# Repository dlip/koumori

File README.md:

# Koumori Keyboard

- Designed to be minimalistic and portable
- 28 keys (Using Engram with my [layout](https://github.com/dlip/qmk_firmware/blob/dlip/keyboards/dlip/koumori/keymaps/engram/README.md))
- Unibody design
- RP2040-Zero MCU
- Cirque 40mm trackpad with glass overlay
- Customizable layout with QMK Firmware
- Case with handle and magnetic lid
- PCB and case designed in [Ergogen](https://ergogen.xyz)
- Simple [build guide](./build.md) with no microscopic parts
- Name means the animal "bat" in Japanese
- Open source and free (GPL-3.0)

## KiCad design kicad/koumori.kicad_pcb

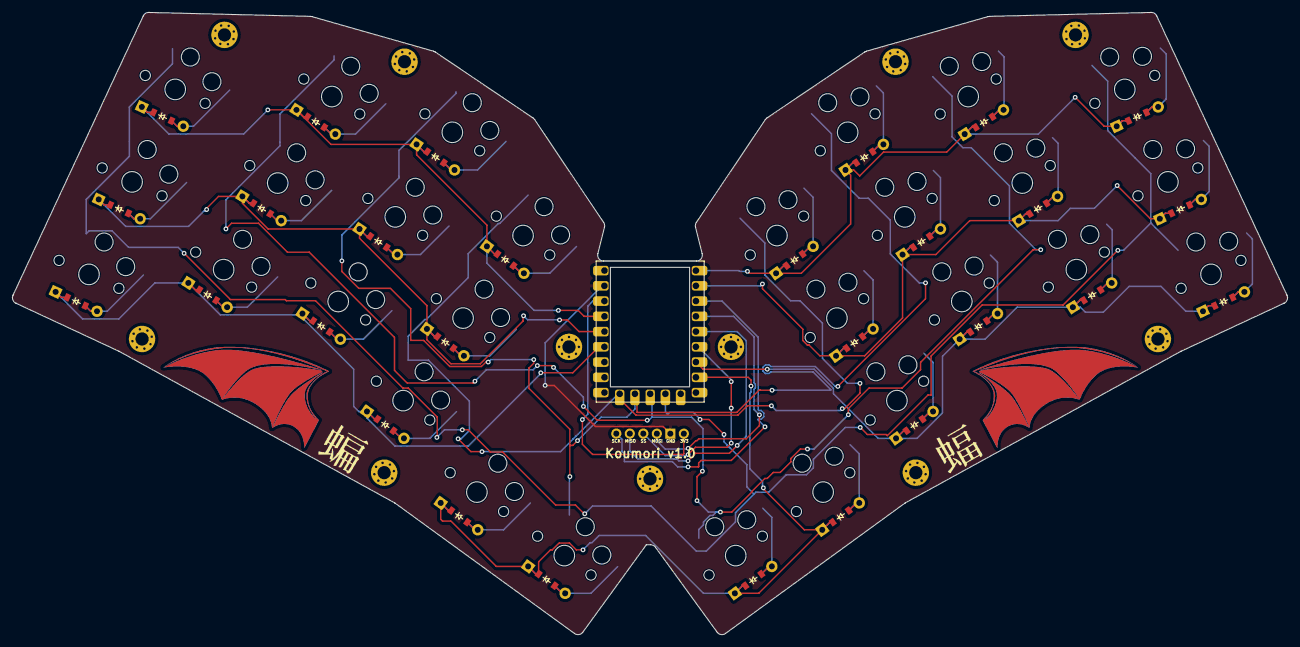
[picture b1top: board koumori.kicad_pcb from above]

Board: 2 copper layers, 212.4 x 103.7 mm, 69 parts (0 on the bottom side), 45 nets.

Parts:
D1, D2, D3, D4, D5, D6, D7, D8, D9, D10, D11, D12, D13, D14, D15, D16, D17, D18, D19, D20, D21, D22, D23, D24, D25, D26, D27, D28: ComboDiode
Pointing1: Pointing-connector
RP2040Zero1: RP2040-Zero
S1, S2, S3, S4, S5, S6, S7, S8, S9, S10, S11, S12, S13, S14, S15, S16, S17, S18, S19, S20, S21, S22, S23, S24, S25, S26, S27, S28: PG1350
_1, _2, _3, _4, _5, _6, _7, _8, _9, _10, _11: MountingHole_2.2mm_M2_Pad_Via

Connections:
GND: Pointing1.5, RP2040Zero1.20
GP0: D17.1, D20.1, D23.1, D26.1, RP2040Zero1.1
GP1: D16.1, D19.1, D22.1, D25.1, RP2040Zero1.2
GP2: Pointing1.1, RP2040Zero1.3
GP3: Pointing1.4, RP2040Zero1.4
GP4: Pointing1.2, RP2040Zero1.5
GP5: Pointing1.3, RP2040Zero1.6
GP6: D15.1, D18.1, D21.1, D24.1, RP2040Zero1.7
GP7: D13.1, D14.1, D27.1, D28.1, RP2040Zero1.8
GP10: RP2040Zero1.11, S1.1, S2.1, S3.1, S15.1, S16.1, S17.1, S27.1
GP11: RP2040Zero1.12, S4.1, S5.1, S6.1, S18.1, S19.1, S20.1, S28.1
GP12: RP2040Zero1.13, S7.1, S8.1, S9.1, S14.1, S21.1, S22.1, S23.1
GP13: RP2040Zero1.14, S10.1, S11.1, S12.1, S13.1, S24.1, S25.1, S26.1
GP27: D1.1, D4.1, D7.1, D10.1, RP2040Zero1.18
GP28: D2.1, D5.1, D8.1, D11.1, RP2040Zero1.22
GP29: D3.1, D6.1, D9.1, D12.1, RP2040Zero1.23
P3V3: Pointing1.6, RP2040Zero1.21
index_bottom: D10.2, S10.2
index_middle: D11.2, S11.2
index_top: D12.2, S12.2
inner_top: D13.2, S13.2
middle_bottom: D7.2, S7.2
middle_middle: D8.2, S8.2
middle_top: D9.2, S9.2
mirror_index_bottom: D24.2, S24.2
mirror_index_middle: D25.2, S25.2
mirror_index_top: D26.2, S26.2
mirror_inner_top: D27.2, S27.2
mirror_middle_bottom: D21.2, S21.2
mirror_middle_middle: D22.2, S22.2
mirror_middle_top: D23.2, S23.2
mirror_outer_top: D28.2, S28.2
mirror_pinky_bottom: D15.2, S15.2
mirror_pinky_middle: D16.2, S16.2
mirror_pinky_top: D17.2, S17.2
mirror_ring_bottom: D18.2, S18.2
mirror_ring_middle: D19.2, S19.2
mirror_ring_top: D20.2, S20.2
outer_top: D14.2, S14.2
pinky_bottom: D1.2, S1.2
pinky_middle: D2.2, S2.2
pinky_top: D3.2, S3.2
ring_bottom: D4.2, S4.2
ring_middle: D5.2, S5.2
ring_top: D6.2, S6.2

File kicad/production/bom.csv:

Designator,Footprint,Quantity,Value,LCSC Part #
"D1, D10, D11, D12, D13, D14, D15, D16, D17, D18, D19, D2, D20, D21, D22, D23, D24, D25, D26, D27, D28, D3, D4, D5, D6, D7, D8, D9",ComboDiode,28,,
POINTING1,Pointing-connector,1,,
RP2040ZERO1,RP2040-Zero,1,,
"S1, S10, S11, S12, S13, S14, S15, S16, S17, S18, S19, S2, S20, S21, S22, S23, S24, S25, S26, S27, S28, S3, S4, S5, S6, S7, S8, S9",PG1350,28,,
"_1, _10, _11, _2, _3, _4, _5, _6, _7, _8, _9",MountingHole_2.2mm_M2_Pad_Via,11,,

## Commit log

2026-02-16 Koumori v1.0
2026-02-16 Readme
2026-02-16 Add magnet link
2026-02-16 Add cirque overlay
